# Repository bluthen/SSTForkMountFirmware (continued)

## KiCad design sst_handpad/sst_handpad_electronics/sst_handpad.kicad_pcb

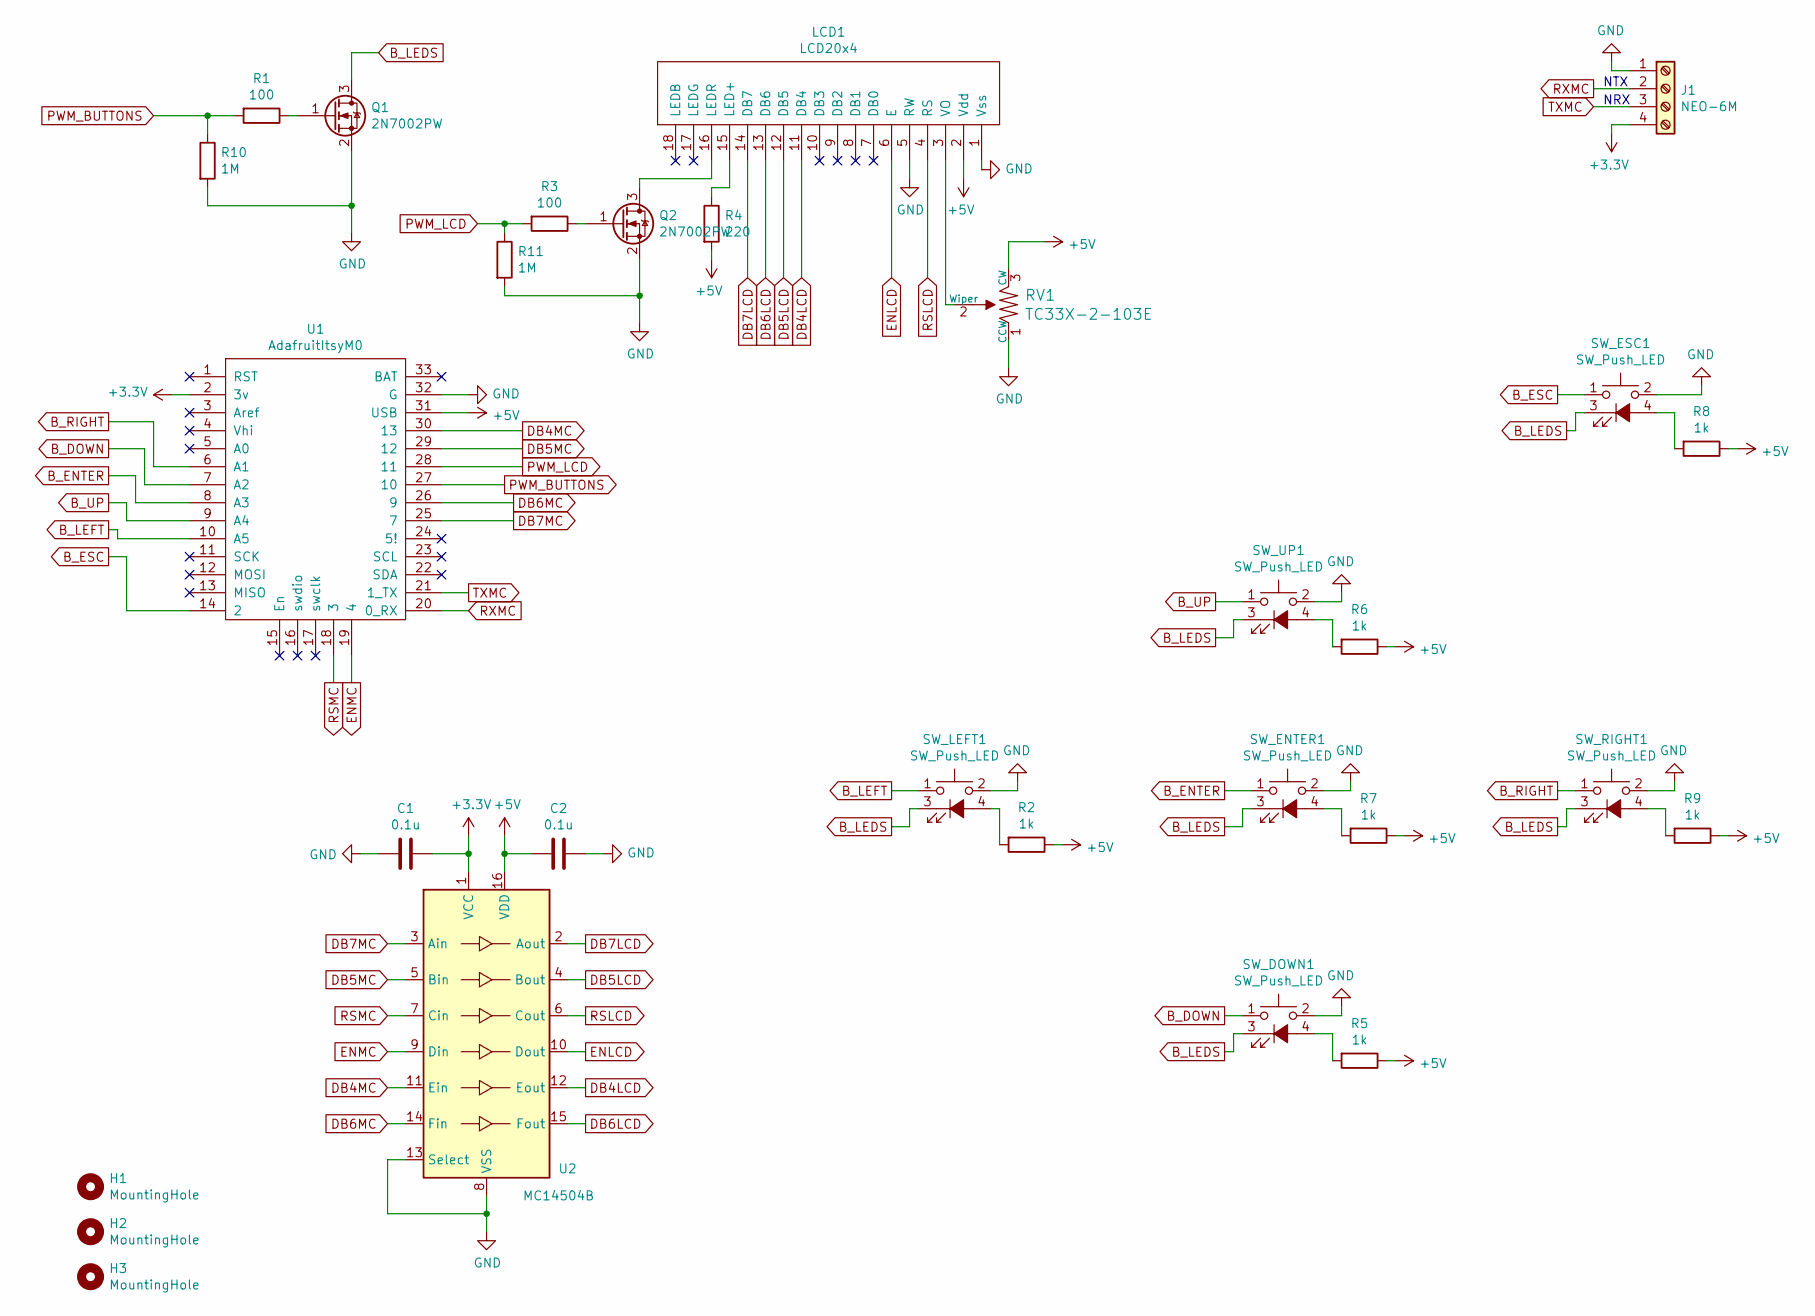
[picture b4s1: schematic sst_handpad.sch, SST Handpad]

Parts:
C1, C2: 0.1u; C_0603_HandSoldering
H1, H2, H3: MountingHole; MountingHole_3.2mm_M3
J1: NEO-6M; 1X04_LOCK_LONGPADS
LCD1: LCD20x4; 1X16_LOCK_LONGPADS
Q1, Q2: 2N7002PW; SOT-323_SC-70_Handsoldering
R1, R3: 100; R_0603_HandSoldering
R2, R5, R6, R7, R8, R9: 1k; R_0603_HandSoldering
R4: 220; R_0603_HandSoldering
R10, R11: 1M; R_0603_HandSoldering
RV1: TC33X-2-103E; Trimpot_3.8mmx3.6mm_TC33X-2-103E; MPN TC33X-2-103E; Digi-Key_PN TC33X-103ETR-ND
SW_DOWN1: SW_Push_LED; MPJA_LED_SWITCH
SW_ENTER1: SW_Push_LED; MPJA_LED_SWITCH
SW_ESC1: SW_Push_LED; MPJA_LED_SWITCH
SW_LEFT1: SW_Push_LED; MPJA_LED_SWITCH
SW_RIGHT1: SW_Push_LED; MPJA_LED_SWITCH
SW_UP1: SW_Push_LED; MPJA_LED_SWITCH
U1: AdafruitItsyM0; ItsyBitsyM0Exp
U2: MC14504B; SOIC-16_3.9x9.9mm_Pitch1.27mm

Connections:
+3V3: C1.2, J1.4, U1.2 (3v), U2.1 (VCC)
+5V: C2.2, LCD1.2 (Vdd), R2.1, R4.2, R5.1, R6.1, R7.1, R8.1, R9.1, RV1.3 (CW), U1.31 (USB), U2.16 (VDD)
B_DOWN: SW_DOWN1.1, U1.7 (A2)
B_ENTER: SW_ENTER1.1, U1.8 (A3)
B_ESC: SW_ESC1.1, U1.14 (2)
B_LEDS: Q1.3 (D), SW_DOWN1.3 (K), SW_ENTER1.3 (K), SW_ESC1.3 (K), SW_LEFT1.3 (K), SW_RIGHT1.3 (K), SW_UP1.3 (K)
B_LEFT: SW_LEFT1.1, U1.10 (A5)
B_RIGHT: SW_RIGHT1.1, U1.6 (A1)
B_UP: SW_UP1.1, U1.9 (A4)
DB4LCD: LCD1.11 (DB4), U2.12 (Eout)
DB4MC: U1.30 (13), U2.11 (Ein)
DB5LCD: LCD1.12 (DB5), U2.4 (Bout)
DB5MC: U1.29 (12), U2.5 (Bin)
DB6LCD: LCD1.13 (DB6), U2.15 (Fout)
DB6MC: U1.26 (9), U2.14 (Fin)
DB7LCD: LCD1.14 (DB7), U2.2 (Aout)
DB7MC: U1.25 (7), U2.3 (Ain)
ENLCD: LCD1.6 (E), U2.10 (Dout)
ENMC: U1.19 (4), U2.9 (Din)
GND: C1.1, C2.1, J1.1, LCD1.1 (Vss), LCD1.5 (RW), Q1.2 (S), Q2.2 (S), R10.2, R11.2, RV1.1 (CCW), SW_DOWN1.2, SW_ENTER1.2, SW_ESC1.2, SW_LEFT1.2, SW_RIGHT1.2, SW_UP1.2, U1.32 (G), U2.8 (VSS), U2.13 (Select)
unnamed: LCD1.3 (VO), RV1.2 (Wiper)
unnamed: LCD1.15 (LED+), R4.1
unnamed: LCD1.16 (LEDR), Q2.3 (D)
unnamed: Q1.1 (G), R1.1
unnamed: Q2.1 (G), R3.1
unnamed: R2.2, SW_LEFT1.4 (A)
unnamed: R5.2, SW_DOWN1.4 (A)
unnamed: R6.2, SW_UP1.4 (A)
unnamed: R7.2, SW_ENTER1.4 (A)
unnamed: R8.2, SW_ESC1.4 (A)
unnamed: R9.2, SW_RIGHT1.4 (A)
PWM_BUTTONS: R1.2, R10.1, U1.27 (10)
PWM_LCD: R3.2, R11.1, U1.28 (11)
RSLCD: LCD1.4 (RS), U2.6 (Cout)
RSMC: U1.18 (3), U2.7 (Cin)
RXMC: J1.2, U1.20 (0_RX)
TXMC: J1.3, U1.21 (1_TX)

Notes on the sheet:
NTX
NRX

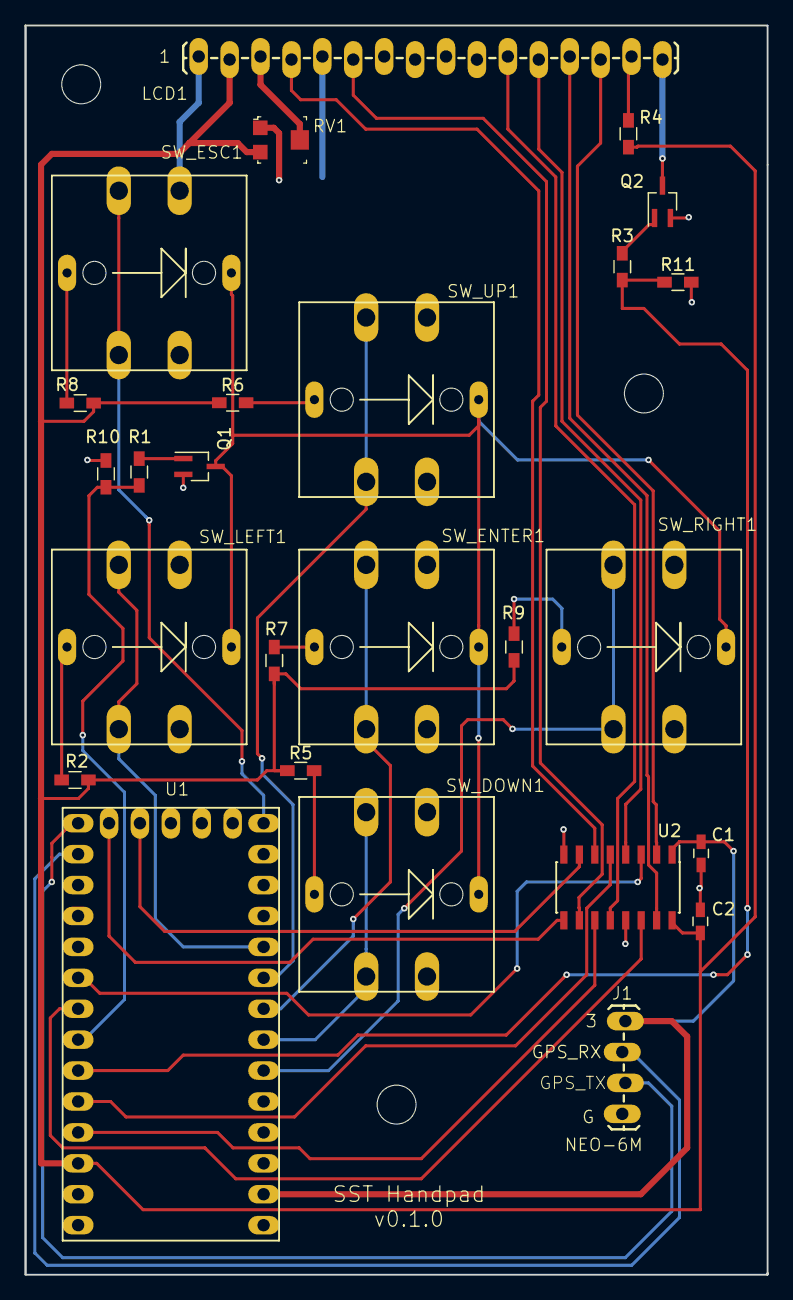
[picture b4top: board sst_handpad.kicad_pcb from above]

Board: 2 copper layers, 60.9 x 102.6 mm, 29 parts (0 on the bottom side), 37 nets.

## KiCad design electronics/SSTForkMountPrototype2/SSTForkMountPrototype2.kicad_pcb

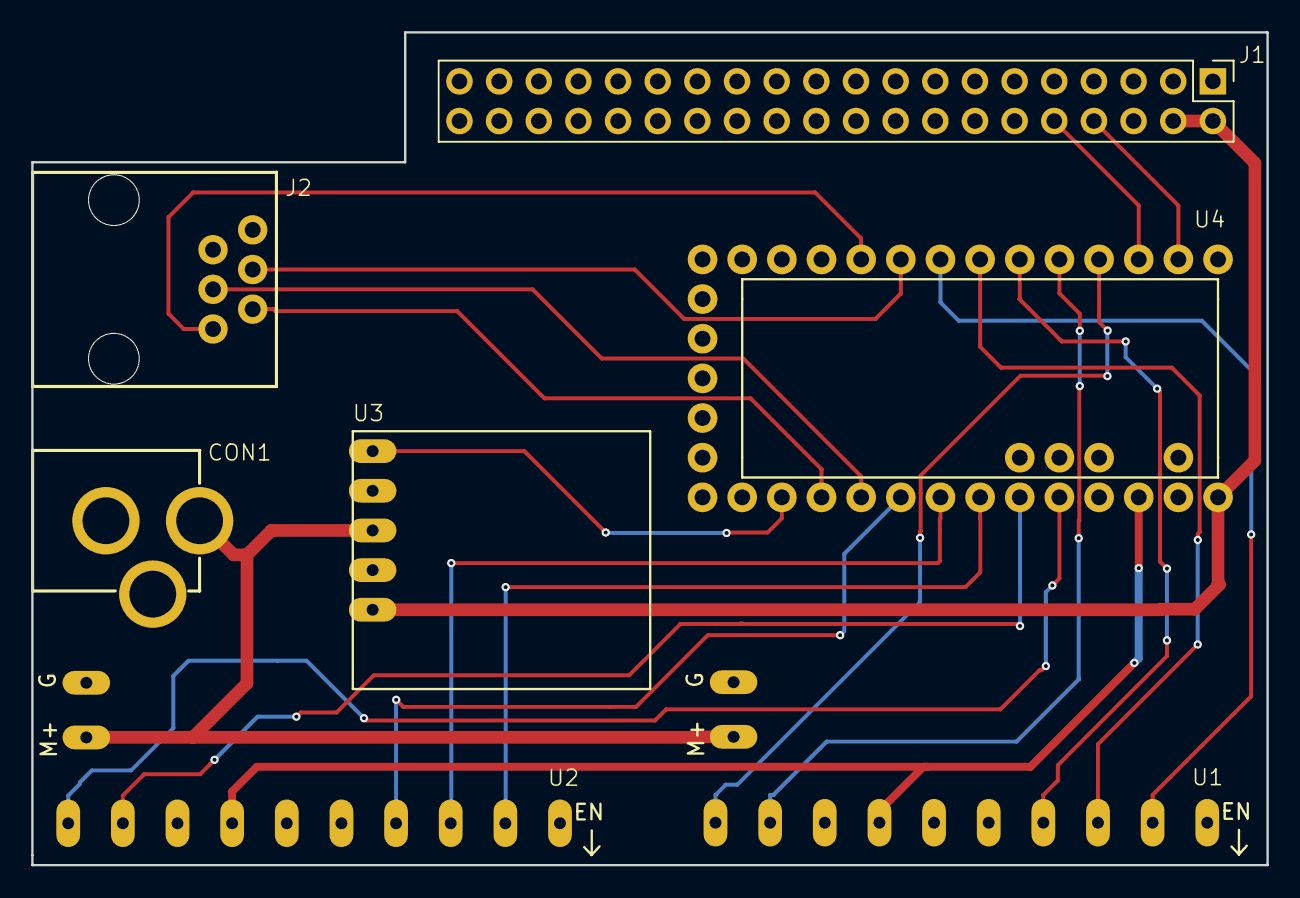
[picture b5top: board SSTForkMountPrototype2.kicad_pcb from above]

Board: 2 copper layers, 79.1 x 53.3 mm, 7 parts (0 on the bottom side), 21 nets.

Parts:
CON1: BARREL_JACK; POWER_JACK_PTH
J1: Raspberry_Pi_2_3; Pin_Header_Straight_2x20_Pitch2.54mm
J2: RJ12; RJ11-6
U1, U2: SparkFun_BigEasyDriver; bigeasy_front3.5
U3: pololu_D24V22F5
U4: Teensy_3.1; Teensy-3.1

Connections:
+3V3: U1.7, U2.7, U4.24
+5V: J1.2, J1.4, U3.5, U4.26
AG_DEC+Y: J2.5, U4.16
AG_DEC-Y: J2.4, U4.17
AG_RA+X: J2.6, U4.8
AG_RA-X: J2.3, U4.7
DEC_DIR: U2.10, U4.22
DEC_MS1: U2.2, U4.20
DEC_MS2: U2.3, U4.19
DEC_MS3: U2.4, U4.18
DEC_STEP: U2.9, U4.21
GND: CON1.2, CON1.3, J1.6, J1.9, J1.14, J1.20, J1.25, J1.30, J1.34, J1.39, J2.2, U1.8, U1.15, U2.8, U2.15, U3.4, U4.27
PG: U3.1, U4.15
RA_DIR: U1.10, U4.2
RA_MS1: U1.2, U4.6
RA_MS2: U1.3, U4.5
RA_MS3: U1.4, U4.4
RA_STEP: U1.9, U4.3
RPI_RX: J1.10, U4.1
RPI_TX: J1.8, U4.0
VDC: CON1.1, U1.16, U2.16, U3.3

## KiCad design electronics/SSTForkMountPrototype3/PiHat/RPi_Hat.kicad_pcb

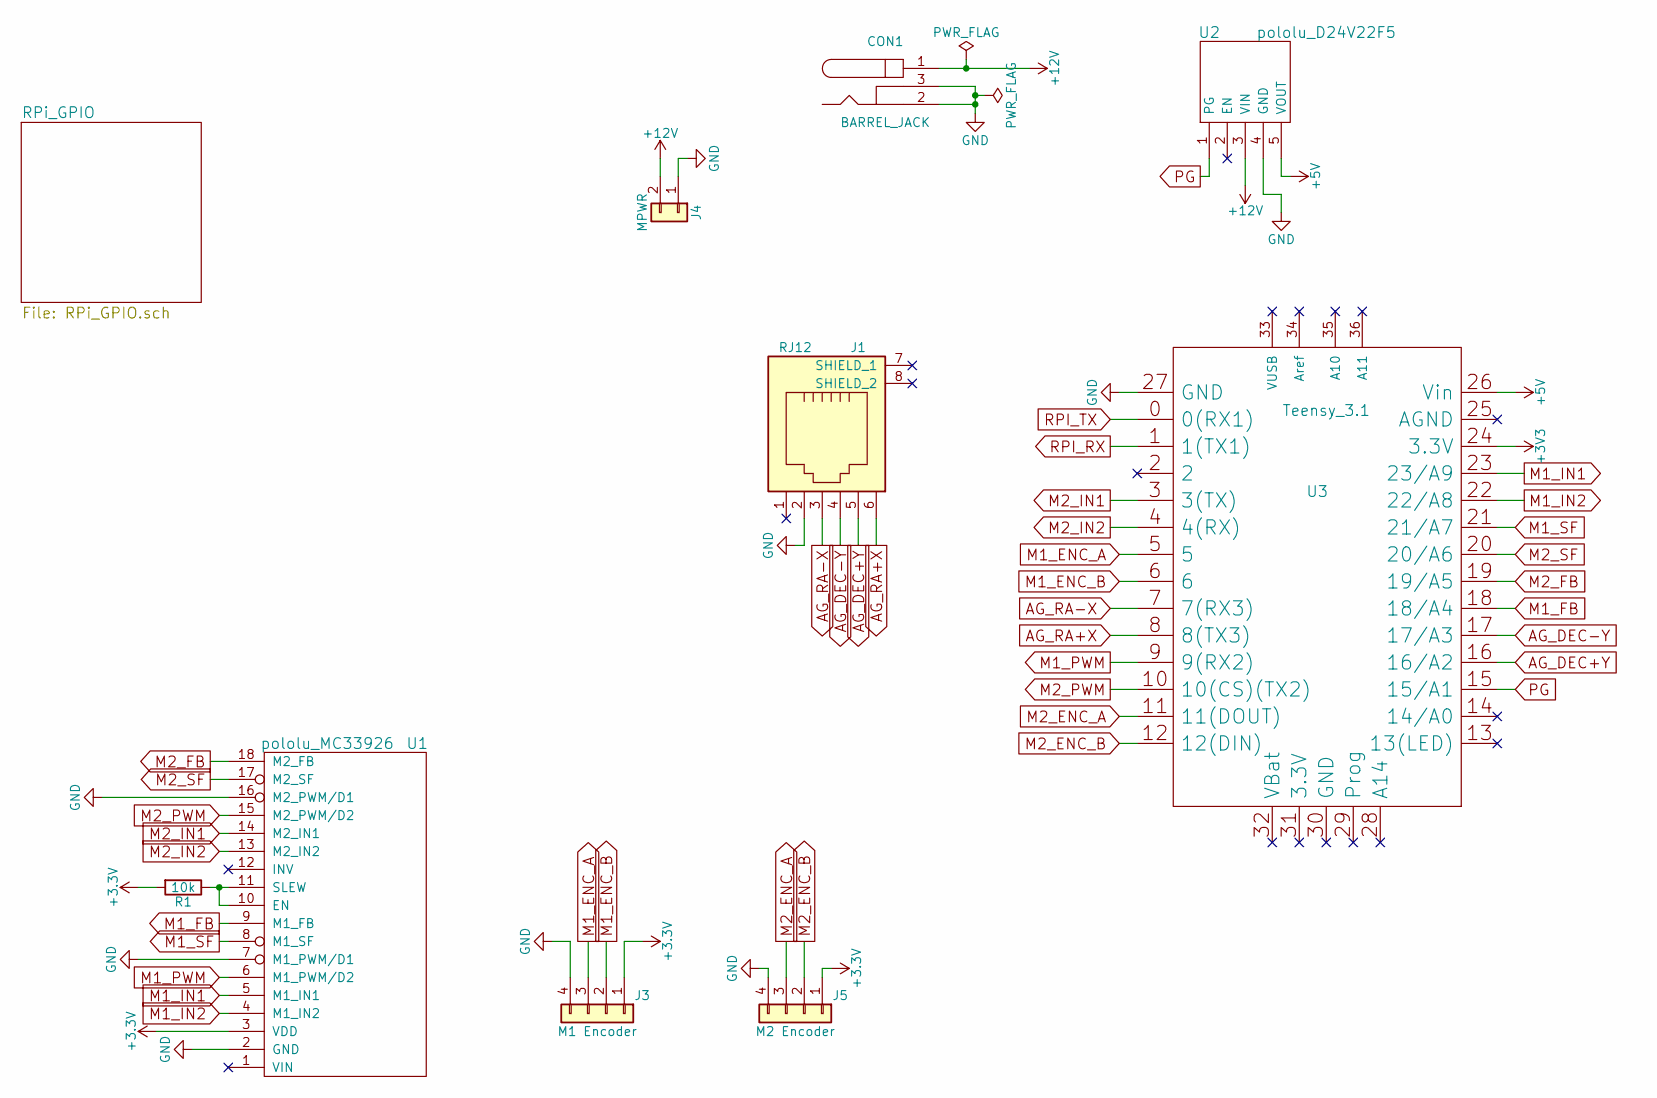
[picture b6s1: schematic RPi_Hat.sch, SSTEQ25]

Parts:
CON1: BARREL_JACK; POWER_JACK_PTH
J1: RJ12; RJ11-6
J3: M1 Encoder; 1X04_LOCK_LONGPADS
J4: MPWR; 1X02_LOCK_LONGPADS
J5: M2 Encoder; 1X04_LOCK_LONGPADS
R1: 10k; R_0603
U1: pololu_MC33926; 1X18
U2: pololu_D24V22F5
U3: Teensy_3.1; Teensy-3.1

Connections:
+5V: U2.5 (VOUT), U3.26 (Vin); also elsewhere on the board
+12V: CON1.1, J4.2, U2.3 (VIN)
AG_DEC+Y: J1.5, U3.16 (16/A2)
AG_DEC-Y: J1.4, U3.17 (17/A3)
AG_RA+X: J1.6, U3.8 (8(TX3))
AG_RA-X: J1.3, U3.7 (7(RX3))
GND: CON1.2, CON1.3, J1.2, J3.4, J4.1, J5.4, U1.2 (GND), U1.7 (M1_PWM/D1), U1.16 (M2_PWM/D1), U2.4 (GND), U3.27 (GND); also elsewhere on the board
M1_ENC_A: J3.3, U3.5
M1_ENC_B: J3.2, U3.6
M1_FB: U1.9 (M1_FB), U3.18 (18/A4)
M1_IN1: U1.5 (M1_IN1), U3.23 (23/A9)
M1_IN2: U1.4 (M1_IN2), U3.22 (22/A8)
M1_PWM: U1.6 (M1_PWM/D2), U3.9 (9(RX2))
M1_SF: U1.8 (M1_SF), U3.21 (21/A7)
M2_ENC_A: J5.3, U3.11 (11(DOUT))
M2_ENC_B: J5.2, U3.12 (12(DIN))
M2_FB: U1.18 (M2_FB), U3.19 (19/A5)
M2_IN1: U1.14 (M2_IN1), U3.3 (3(TX))
M2_IN2: U1.13 (M2_IN2), U3.4 (4(RX))
M2_PWM: U1.15 (M2_PWM/D2), U3.10 (10(CS)(TX2))
M2_SF: U1.17 (M2_SF), U3.20 (20/A6)
unnamed: R1.1, U1.10 (EN), U1.11 (SLEW)
PG: U2.1 (PG), U3.15 (15/A1)
RPI_RX: U3.1 (1(TX1)); also elsewhere on the board
RPI_TX: U3.0 (0(RX1)); also elsewhere on the board

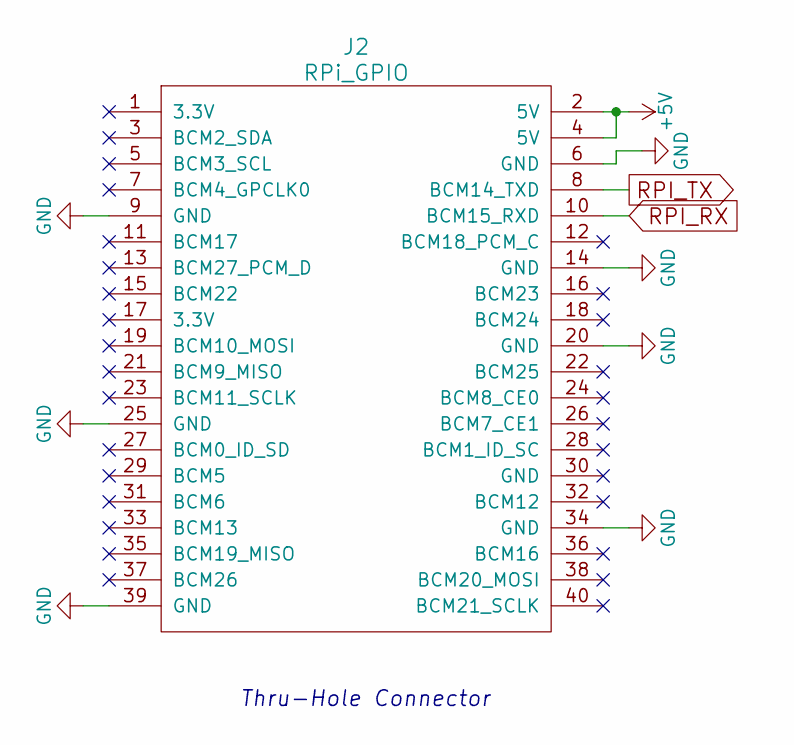
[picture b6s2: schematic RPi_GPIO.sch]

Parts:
J2: RPi_GPIO; Pin_Header_Straight_2x20

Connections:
+5V: J2.2 (5V), J2.4 (5V); also elsewhere on the board
GND: J2.6 (GND), J2.9 (GND), J2.14 (GND), J2.20 (GND), J2.25 (GND), J2.34 (GND), J2.39 (GND); also elsewhere on the board
RPI_RX: J2.10 (BCM15_RXD); also elsewhere on the board
RPI_TX: J2.8 (BCM14_TXD); also elsewhere on the board

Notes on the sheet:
Thru-Hole Connector

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
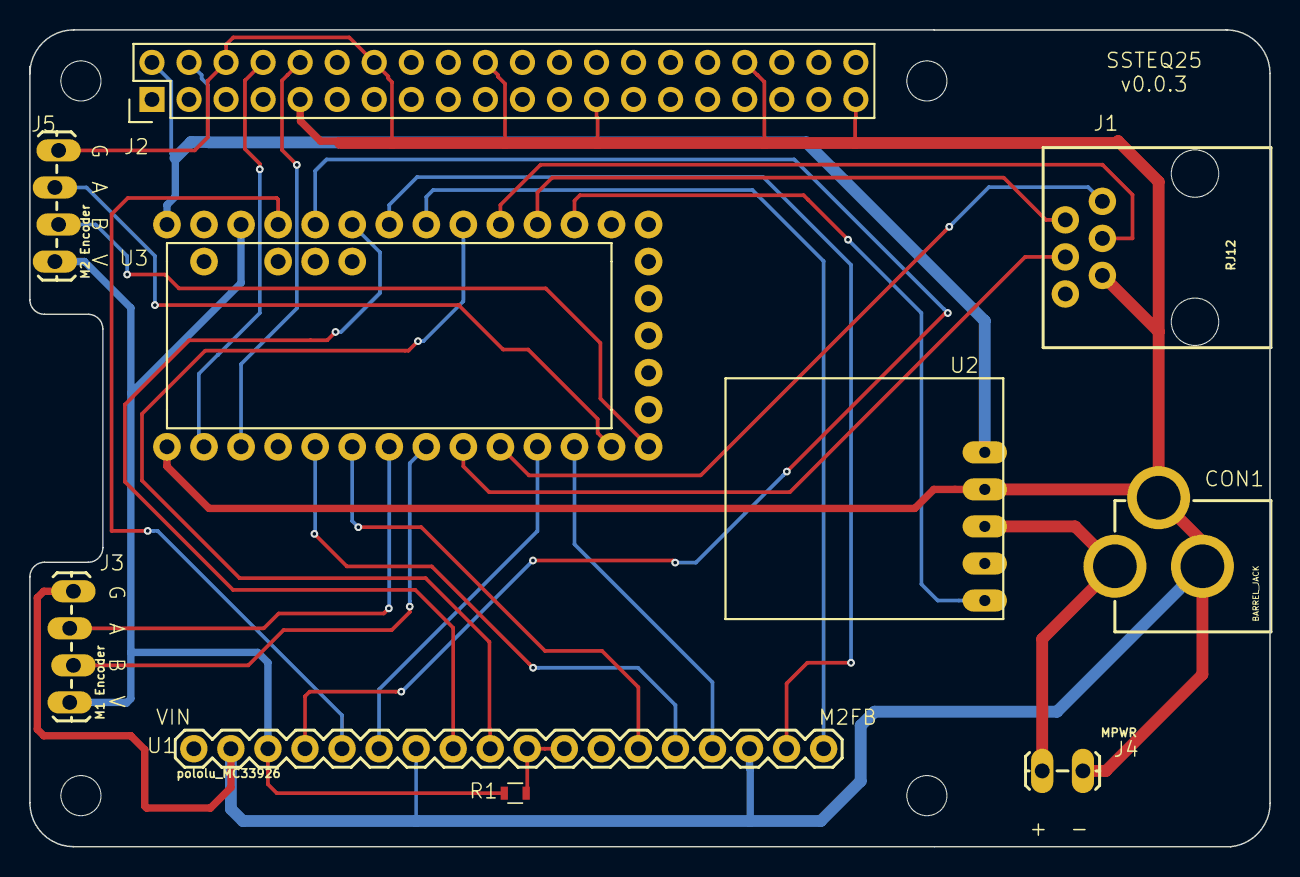
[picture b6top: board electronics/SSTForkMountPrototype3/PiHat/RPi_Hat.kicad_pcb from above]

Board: 2 copper layers, 85.0 x 56.0 mm, 10 parts (0 on the bottom side), 26 nets.

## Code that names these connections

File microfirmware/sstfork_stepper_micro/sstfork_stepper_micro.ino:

#include <Wire.h>
#include <inttypes.h>
#include <stdint.h>

#include "command.h"
#include "forkmount.h"
#include "stepper.h"

const char *sstversion = "v1.1.0";
Stepper *raStepper = NULL;
Stepper *decStepper = NULL;


static const int RA_ENC_A_PIN = 5;
static const int RA_ENC_B_PIN = 3;
static const int DEC_ENC_A_PIN = 2;
static const int DEC_ENC_B_PIN = 4;

static const int RA_DIR_PIN = 7;
static const int RA_STEP_PIN = 8;
static const int RA_CS_PIN = 10;
static const int RA_MISO_PIN = 16;
static const int RA_SCK_PIN = 18;
static const int RA_MOSI_PIN = 19;

static const int DEC_DIR_PIN = 14;
static const int DEC_STEP_PIN = 15;
static const int DEC_CS_PIN = 17;
static const int DEC_MISO_PIN = 16;
static const int DEC_SCK_PIN = 18;
static const int DEC_MOSI_PIN = 19;

static const int LED_PIN = 13;

const static int AUTOGUIDE_DEC_NEGY_PIN = 21;
const static int AUTOGUIDE_DEC_POSY_PIN = 22;
const static int AUTOGUIDE_RA_NEGX_PIN = 20;
const static int AUTOGUIDE_RA_POSX_PIN = 23;

bool sst_debug = false;

static Command* piCommand = NULL;
static Command* usbCommand = NULL;
IntervalTimer stepperTimer;

void autoguide_init() {
  pinMode(AUTOGUIDE_DEC_NEGY_PIN, INPUT);
  digitalWrite(AUTOGUIDE_DEC_NEGY_PIN, HIGH);
  pinMode(AUTOGUIDE_DEC_POSY_PIN, INPUT);
  digitalWrite(AUTOGUIDE_DEC_POSY_PIN, HIGH);
  pinMode(AUTOGUIDE_RA_NEGX_PIN, INPUT);
  digitalWrite(AUTOGUIDE_RA_NEGX_PIN, HIGH);
  pinMode(AUTOGUIDE_RA_POSX_PIN, INPUT);
  digitalWrite(AUTOGUIDE_RA_POSX_PIN, HIGH);
}

/**
 * When first powered up. sets up serial, sstvars, stepper, console, resets
 * tracker.
 */
void setup() {
  pinMode(DEC_CS_PIN, OUTPUT);
  digitalWrite(DEC_CS_PIN, HIGH);
  pinMode(RA_CS_PIN, OUTPUT);
  digitalWrite(RA_CS_PIN, HIGH);
  pinMode(LED_PIN, OUTPUT);
  digitalWrite(LED_PIN, HIGH);

  while (!Serial && millis() < 2000) {

  }
  digitalWrite(LED_PIN, LOW);
  if (Serial) {
    Serial.begin(115200);
    usbCommand = new Command(&Serial);
  }
  Serial1.begin(115200);
  piCommand = new Command(&Serial1);

  delay(1000);
  if (Serial) {
    DEBUG_SERIAL.println("Begin");
  }
  //SPI.begin();

  decStepper = new Stepper(DEC_DIR_PIN, DEC_STEP_PIN,
                           DEC_CS_PIN, DEC_MISO_PIN, DEC_MOSI_PIN, DEC_SCK_PIN, 
                           2, DEC_ENC_A_PIN, DEC_ENC_B_PIN, 1);
  raStepper = new Stepper(RA_DIR_PIN, RA_STEP_PIN,
                          RA_CS_PIN, RA_MISO_PIN, RA_MOSI_PIN, RA_SCK_PIN, 
                          1, RA_ENC_A_PIN, RA_ENC_B_PIN, 0);

  //raStepper->setSpeed(0.0);
  //decStepper->setSpeed(0.0);
  autoguide_init();
  stepperTimer.begin(update, 4);
  if (Serial && usbCommand != NULL) {
    Serial.print(F("StarSync Tracker Fork Mount "));
    Serial.println(sstversion);
    Serial.print("$ ");
  }
  Serial1.print(F("StarSync Tracker Fork Mount "));
  Serial1.println(sstversion);
  Serial1.print("$ ");
}

uint8_t status = 0;
uint8_t debounce_status = 255;
uint8_t prev_status = 255;
uint8_t rate_state = 0;

const uint8_t AG_POSY_MASK = 0;
const uint8_t AG_NEGY_MASK = 1;
const uint8_t AG_NEGX_MASK = 2;
const uint8_t AG_POSX_MASK = 3;

unsigned long lastDebounceTime = 0;
unsigned long debounceDelay = 50;

void autoguide_read() {
  status = digitalRead(AUTOGUIDE_DEC_POSY_PIN) << AG_POSY_MASK;
  status |= digitalRead(AUTOGUIDE_DEC_NEGY_PIN) << AG_NEGY_MASK;
  status |= digitalRead(AUTOGUIDE_RA_NEGX_PIN) << AG_NEGX_MASK;
  status |= digitalRead(AUTOGUIDE_RA_POSX_PIN) << AG_POSX_MASK;
}

void update() {
  raStepper->update();
  decStepper->update();
}

void autoguide_run() {
  if (raStepper->guidingDisabled() && decStepper->guidingDisabled()) {
    return;
  }

  autoguide_read();
  // If change
  if (status != debounce_status) {
    debounce_status = status;
    lastDebounceTime = millis();
  }

  if (status != prev_status && (millis() - lastDebounceTime) > debounceDelay) {
    if (sst_debug) {
      Serial1.print("status != prev_status and debounced: ");
      Serial1.println(status);
    }

    // Low means pressed except for rate switch

    prev_status = status;

    // If no directions are pressed we are just tracking
    if ((status & 0x0F) == 0x0F) {
      raStepper->guide(0);
      decStepper->guide(0);
      if (sst_debug) {
        Serial1.print("no buttons: ");
      }
    } else {
      if (!(status & (1 << AG_POSY_MASK))) {
        decStepper->guide(1);
        if (sst_debug) {
          Serial1.print("DEC up ");
        }
      } else if (!(status & (1 << AG_NEGY_MASK))) {
        decStepper->guide(-1);
        if (sst_debug) {
          Serial1.print("DEC down ");
        }
      } else {
        decStepper->guide(0);
      }

      if (!(status & (1 << AG_POSX_MASK))) {
        raStepper->guide(1);
        if (sst_debug) {
          Serial1.print("RA Right ");
        }

      } else if (!(status & (1 << AG_NEGX_MASK))) {
        raStepper->guide(-1);
        if (sst_debug) {
          Serial1.print("RA Left");
        }
      } else {
        raStepper->guide(0);
      }
    }
  }
}


/**
 * Program loop.
 */
void loop() {
  // Serial.println("Loop");
  autoguide_run();
  piCommand->read();
  if (Serial) {
    if (usbCommand == NULL) {
      Serial.begin(115200);
      usbCommand = new Command(&Serial);
    }
    usbCommand->read();
  }
}

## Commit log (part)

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2017-09-19 some more intial forkmount code
2017-12-20 firmware work
2018-01-02 initial piside commit.
2018-01-02 Incremental progress. manual controls work.
2018-01-02 Quicker status added
2018-01-04 progress
2018-01-05 Starting goto ability
2018-01-06 improve search
2018-01-07 more progress
2018-01-11 using bootstrap, more progress
2018-01-16 Fixed coordinates around poles.
2018-03-02 Added bootstrap and manifest to make a phone bookmark.
2018-03-06 Search spinners, Alt/Az goto/sync, added medium slew speed.
2018-03-12 Fixed disable autoguide error.
2018-03-12 Simulator for the microcontroller on serial port..
2018-03-16 fixed autoguide_enable command
2018-03-16 Fixed when button is pressed and you move mouse off of button.
2018-03-16 Older searches don't get overwritten by newer results.
2018-03-18 redlights color styleing, manual slew acceleration, better goto acceleration, fix on simulation for raspeed, guiding rate is change of rate instead of set rate.
2018-03-19 Fixes
2018-03-19 Able to swtich color schemes from default to night vision
2018-03-22 trim coordinate input
2018-03-23 Fixed reading from micro issues that could cause manual slew to get stuck.
2018-03-23 Added some missing print_prompts in simulator.
2018-03-24 Displays percent error on sync. Fix missing prompt in micro firmware.
2018-03-24 Slewto and set action in search are buttons. Set location in search location is button.
2018-03-27 primitive firmware update.
2018-04-03 Move around sync/slew in object search. Change color of buttons added more icons in buttons. Fixed stellarium server when not synced.
2018-04-10 Fixes entering manual RA coordinates.
2018-04-10 version bump
2018-04-10 lots of fixes with manual coordinates.
2018-04-10 Improved input on mobile.
2018-04-16 Added step slewing, and made closer slewing.
2018-04-16 Fixed some going back and forth forever, but will implement pid controller next for slewing.
2018-04-19 Better slewing and acceleration.
2018-04-20 Fixes for close slewing.
2018-04-21 Support for nunchuck for control.
2018-04-29 Chuck firmware, progress on network settings interface.
2018-05-04 more wifi network progress
2018-05-04 Adding missing popper for bootstrap
2018-05-04 example zip
2018-06-19 Added kicad electronics
2018-06-19 RA DEC to M info
2018-07-28 Direction buttons change brightness when pressed
2018-08-11 Client refactor to use webpack
2018-08-21 prototype4 electronics
2018-09-03 Note on stepper motor test point voltage added.
2018-09-04 Updated notes
2018-09-04 Enable power switch detection to shutdown.
2018-09-16 Start of Polar Align Assist.
2018-09-25 polar align assist work
2018-10-01 Polar align assist calibration image generation.
2018-10-06 Network menu work.
2018-10-08 Better working wifi and ethernet configuration
2018-10-13 Work on horizon limit
2018-10-15 Work to support better dev simulation.
2018-10-15 Improved style a bit, got simulation of polar align working.
2018-10-19 Changed monkey patch order to fix a greenlet threading issue
2018-10-22 Fixed wifi settings when wanting no password.
2018-11-16 defaults added to simulation files
2018-11-16 update git ignore
2018-11-18 Improve lat lon degrees calculation
2018-11-20 start of a arc_center_find for polar alignment assist calibration.
2018-11-21 updated enclosure
2018-11-21 v0.2.0 enclosure
2018-12-04 Fix no unset location in footer.
2018-12-04 Fixed minux on mobile firefox.
2018-12-18 Added support for elevation in location set. Better menu for mobile added.
2018-12-21 Added horizon limit enable disable option. Fixed reloading with hash.
2018-12-27 Cleanup to use more astropy classes.
2019-01-04 Starting N point pointing cal.
2019-01-04 client side changes
2019-01-05 Fixed polar align assist with thread mode, added star clicking and setting rotation axises from three point circle.
2019-01-16 More work done on pointing model
2019-01-27 integrated point model.
2019-02-03 Point model sort of working.
2019-02-03 client side to go with previous commit.
2019-02-03 Improved previous parking detection.
2019-02-03 Fix parking.
2019-02-06 Better wifi client connecting.
2019-02-07 micro firmware that counts steps while guiding.
2019-02-12 Using systemd to start python service and network instead of supervisord
2019-02-18 network setting cleanup
2019-02-22 Added solver to polar align assist.
2019-02-22 Added a seperate config for RA Steps/Degree for pointing.
2019-02-22 seperate ra steps/deg for pointing setting.
2019-02-22 Add option for different pointing models. A initial pointing model graph showing sync points. paa camera clears directory at start.
2019-02-23 smaller, more purple points for point model
2019-03-04 Added pointing model logs.
2019-03-12 Fix starting dnsmasq in autohotspot and ctrl_dnsmasq.
2019-03-12 starts avahi service at startup
2019-03-15 Added hostname for network checks.
2019-03-15 Client detects disconnects and host change.
2019-03-15 removes pyc files at start
2019-03-15 example zip script
2019-03-17 dnsmasq eth0 workaround if eth0 is not plugged in on boot.
2019-03-19 Made polar alignment more responsive to changes and error reslienant.
2019-04-12 Added two new pointing models. Added freecad files for electronics enclosure. avahi broadcasting added.
2019-04-12 Encoder counts added to status.
2019-04-14 Added stepper ticks in encoder pulse to status commands.
2019-04-25 Fix issue where sometimes slew would never finish.
2019-06-24 Start of different pointing_model and lx200 protocol support.
2019-06-24 some lx200 protocol fixes
2019-07-07 lx200 slewing busy is fixed. Always thinks at park position now, or if no park position set, at 10/180 alt/az.
2019-07-19 Cleanup of server code to use hour angle dec, instead of alt-az.
2019-07-19 remove stellarium_server from starting on startup
2019-08-21 start of react client
2019-09-02 more work on react interface
2019-09-03 removed polar align assist from the api
2019-09-04 goto coordinates auto focus while filling out
2019-09-11 more progres
2019-09-12 snackbar
2019-09-12 array mobx replace
2019-09-16 Back button sorta works using location.hash
2019-09-16 rename client directories.
2019-09-16 update server code to use new directory names
2019-09-17 Added ability to set pointing model.
2019-09-18 optimized imports
2019-09-27 set snackbar_error to false when snackbar is not error
2019-10-07 work for better goto more smooth acceleration.
2019-10-07 comment out some debugging prints
2019-10-07 Added compression and production build of client in client_main.
2019-10-07 maybe improve slew
2019-10-07 fixed negative deg conversion
2019-10-08 RA and DEC slew in seperate threads. Fixed Coordinate error clearing in UI.
2019-10-11 More configurable encoder graphs
2019-10-14 added csv parser
2019-10-14 missing log update_settings in stepper_control. Logging of last ticks per encoder.
2019-10-14 status gives you last ticks per encoder.
2019-10-14 remove 1 postfix on item names in tritransferlist.
2019-10-14 Fixed default park position
2019-10-16 single steps when speed more than an amount
2019-10-16 define for full step threshold
2019-10-17 added single step switching at high v for faster slewing.
2019-10-19 client_id for manual slew, and negatives allowed in advanced settings
2019-10-19 advanced settings negative input fix
2019-10-22 models don't tottally error when in use.
2019-12-30 Sync changes that can hopfully fix when we can't sync.
2020-03-02 RA/DEC Motor Disable options
2020-03-03 Motors stop if encoders are not reading.
2020-03-05 Fix dec0deg sign issue in lx200 protocol.
2020-03-05 Fix hms to deg ra conversion in goto coordinates interface.
2020-03-11 Added calibration logging feature.
2020-03-17 Info dialog during firmware version update.
2020-03-29 Start of new handpad code.
2020-03-31 more handpad progress
2020-04-03 Better manual coord select and num input.
2020-04-07 Can stop a slew with handpad.
2020-04-08 Handpad changes: display_sleep timeout, communication failure with mount timeout
2020-06-01 added gps support
2020-06-02 handpad work
2020-06-05 First version of a arduino version of handpad firmware.
2020-06-05 Working version of arduino firmware.
2020-06-06 Updated handpad with bosses and virtical micro, and rotated lcd pins
2020-06-07 Removed mosfet switching. Seperate DEC/RA encoder headers.
2020-06-09 proper lock in handpad_server and set last_status to none with a timeout in manual slew.
2020-06-22 Handpad alt/az goto menu added. Clear calibration points button added to web.
2020-06-22 Added Sun as a solar system object. commented handpad debug print statements.
2020-06-22 Import and export settings ability.
2020-07-05 remove circular import
2020-07-18 Progress to a more read only firmware on pi.
2020-07-19 More work for read-only flash
2020-07-20 zipper
2020-07-31 hostapd reorder
2020-08-04 Fixes: 1) Settings upload read-only issue 2) Wifi settings saving 3) Auto Use GPS if handpad plugged in 4) Adds option to pick from themes, currently default and dark 5) Wifi Client connect dialog go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
2020-08-04 Stops ntp. Post_update to turn off predictable net interfaces.
2020-08-06 Adds sidereal time to web interfaces. Adds mount info menu in handpad.
2020-08-07 CPU Info (temperature, cpu load, ram usage) added.
2020-08-31 Fix being able to go dec and ra same time with handpad
2020-09-26 wifi reinit on startup
2020-09-26 version bump extra logging rest api
2020-09-27 Adds goto steps
2020-10-01 allows zero steps
2020-10-03 Fix prefixed zeros in coordinates input. In object search Catalog search don't need spaces anymore.
2020-10-04 cleanup, and should be a real fix for sometime motor direction wrong on startup.
2020-12-12 Fixes with new coordinate system.
2020-12-12 sleep in handpad
2020-12-13 Better unit tests, fixed errors found while unit testing.
2020-12-14 More fixes found by unit testing.
2020-12-14 Added unit test for frame args.
2020-12-14 Fixed up model with coordinate changes.
2020-12-15 Added models and missing files
2020-12-15 more ignore
2020-12-21 Set time changes for lx200 protocol
2020-12-22 Fix lx200 settime
2020-12-29 Fixed negative inputs. Fixed HADec no tracking status. Fixed infinite slew. Added reverse voltage mosfet.
2020-12-29 Added frame to slewing dialog. Fixed network to change /etc/hosts Uses PID controller for settling.
2021-03-29 astrotime fix
2021-04-26 Fix coordinate conversion for affine model.
2021-05-25 Stepper and Brushed Servo boards, stepper uses toshiba driver.
2021-05-25 Updated micro firmware for toshiba driver.
2024-03-02 stepper class using interrupt timers for step/dir instead of loop
2024-04-24 firmware that tries to use TMCStepper for TMC5160.
2024-06-05 Adding new current options to UI.
2024-06-08 Stepper SPI controller board designed for TMC5160
2024-06-16 Updated JS libs, python, and sim, also support MTC stepper options
2024-06-19 some fixes to lx200 protocol. react18 updates.
2024-06-19 Things mostly working after the upgrade.
2024-06-19 Cleaned up lint warnings.
2024-06-20 Added pointing model max points.
2024-08-23 Restructured Advanced Settings.
2024-08-24 slew and guide rate units change to be more friendly.
2024-10-09 minimum current of 1ma. Also can force setCurrents().
2024-10-28 Some basic backlash support.
2024-11-10 dedge to use falling or rising edge to be a step.
2024-12-23 backlash fixes on serverside
2024-12-24 Fixed long commands to micro.
2024-12-25 lx200 protocol socket server is working a little better now.
2024-12-25 Better debugging to serial to ethernet.
2025-01-13 Updated microcontroller firmware to use loop time check stepping instead of interrupts.
2025-01-19 Interrupt based stepper->update()
2025-01-19 update readme.
2025-02-06 high precision toggling.
2025-02-17 Fixes rare hangup when slewing.
2025-02-18 Improved latency on serail to ethernet.
2025-03-11 Fixed guiding pin assignments.
2025-04-25 move position autoguide is enabled in case there is an exception.
2025-04-28 Fix planet coordinate search.
2025-06-09 Will run with docker/podman.
2025-06-09 Added structure diagram.
2025-06-09 White background on structure diagram.
2025-07-09 added __str__ to models to help see what model is doing.
2025-07-09 Fixed __str__ in buiemodel.
2025-07-10 model info debug added.
2025-07-26 Rewrote Buie pointing model
2025-08-03 Added web clienter screenshots
2025-08-03 More cleanup
2025-08-03 Fix typo in readme.
2025-08-04 Better model replacement logic.
2025-08-04 update print line.
2026-02-13 Fixed docker build/up, and fixed DEC issue with 0>dec>-1
2026-02-15 Remove buffer that caused issue with lx200 protocol.
